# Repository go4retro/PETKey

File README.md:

# Commodore VIC/64 to PET/CBM Keyboard Adapter

## Hardware License

Copyright (C) 2021 Jim Brain and RETRO Innovations

These files are free designs; you can redistribute them and/or modify
them under the terms of the Creative Commons Attribution-ShareAlike 
4.0 International License.

You should have received a copy of the license along with this
work. If not, see <http://creativecommons.org/licenses/by-sa/4.0/>.

These files are distributed in the hope that they will be useful,
but WITHOUT ANY WARRANTY; without even the implied warranty of
MERCHANTABILITY or FITNESS FOR A PARTICULAR PURPOSE.  See the
license for more details.

## Software License

Copyright (C) 2021 Jim Brain and RETRO Innovations

These files are free designs; you can redistribute them and/or modify
them under the terms of the GNU General Public License, version 2 as 
published by the Free Software Foundation.

These files are distributed in the hope that they will be useful,
but WITHOUT ANY WARRANTY; without even the implied warranty of
MERCHANTABILITY or FITNESS FOR A PARTICULAR PURPOSE.  See the
GNU General Public License for more details.

You should have received a copy of the GNU General Public License along
with these files; if not, write to the Free Software Foundation, Inc.,
51 Franklin Street, Fifth Floor, Boston, MA 02110-1301 USA.

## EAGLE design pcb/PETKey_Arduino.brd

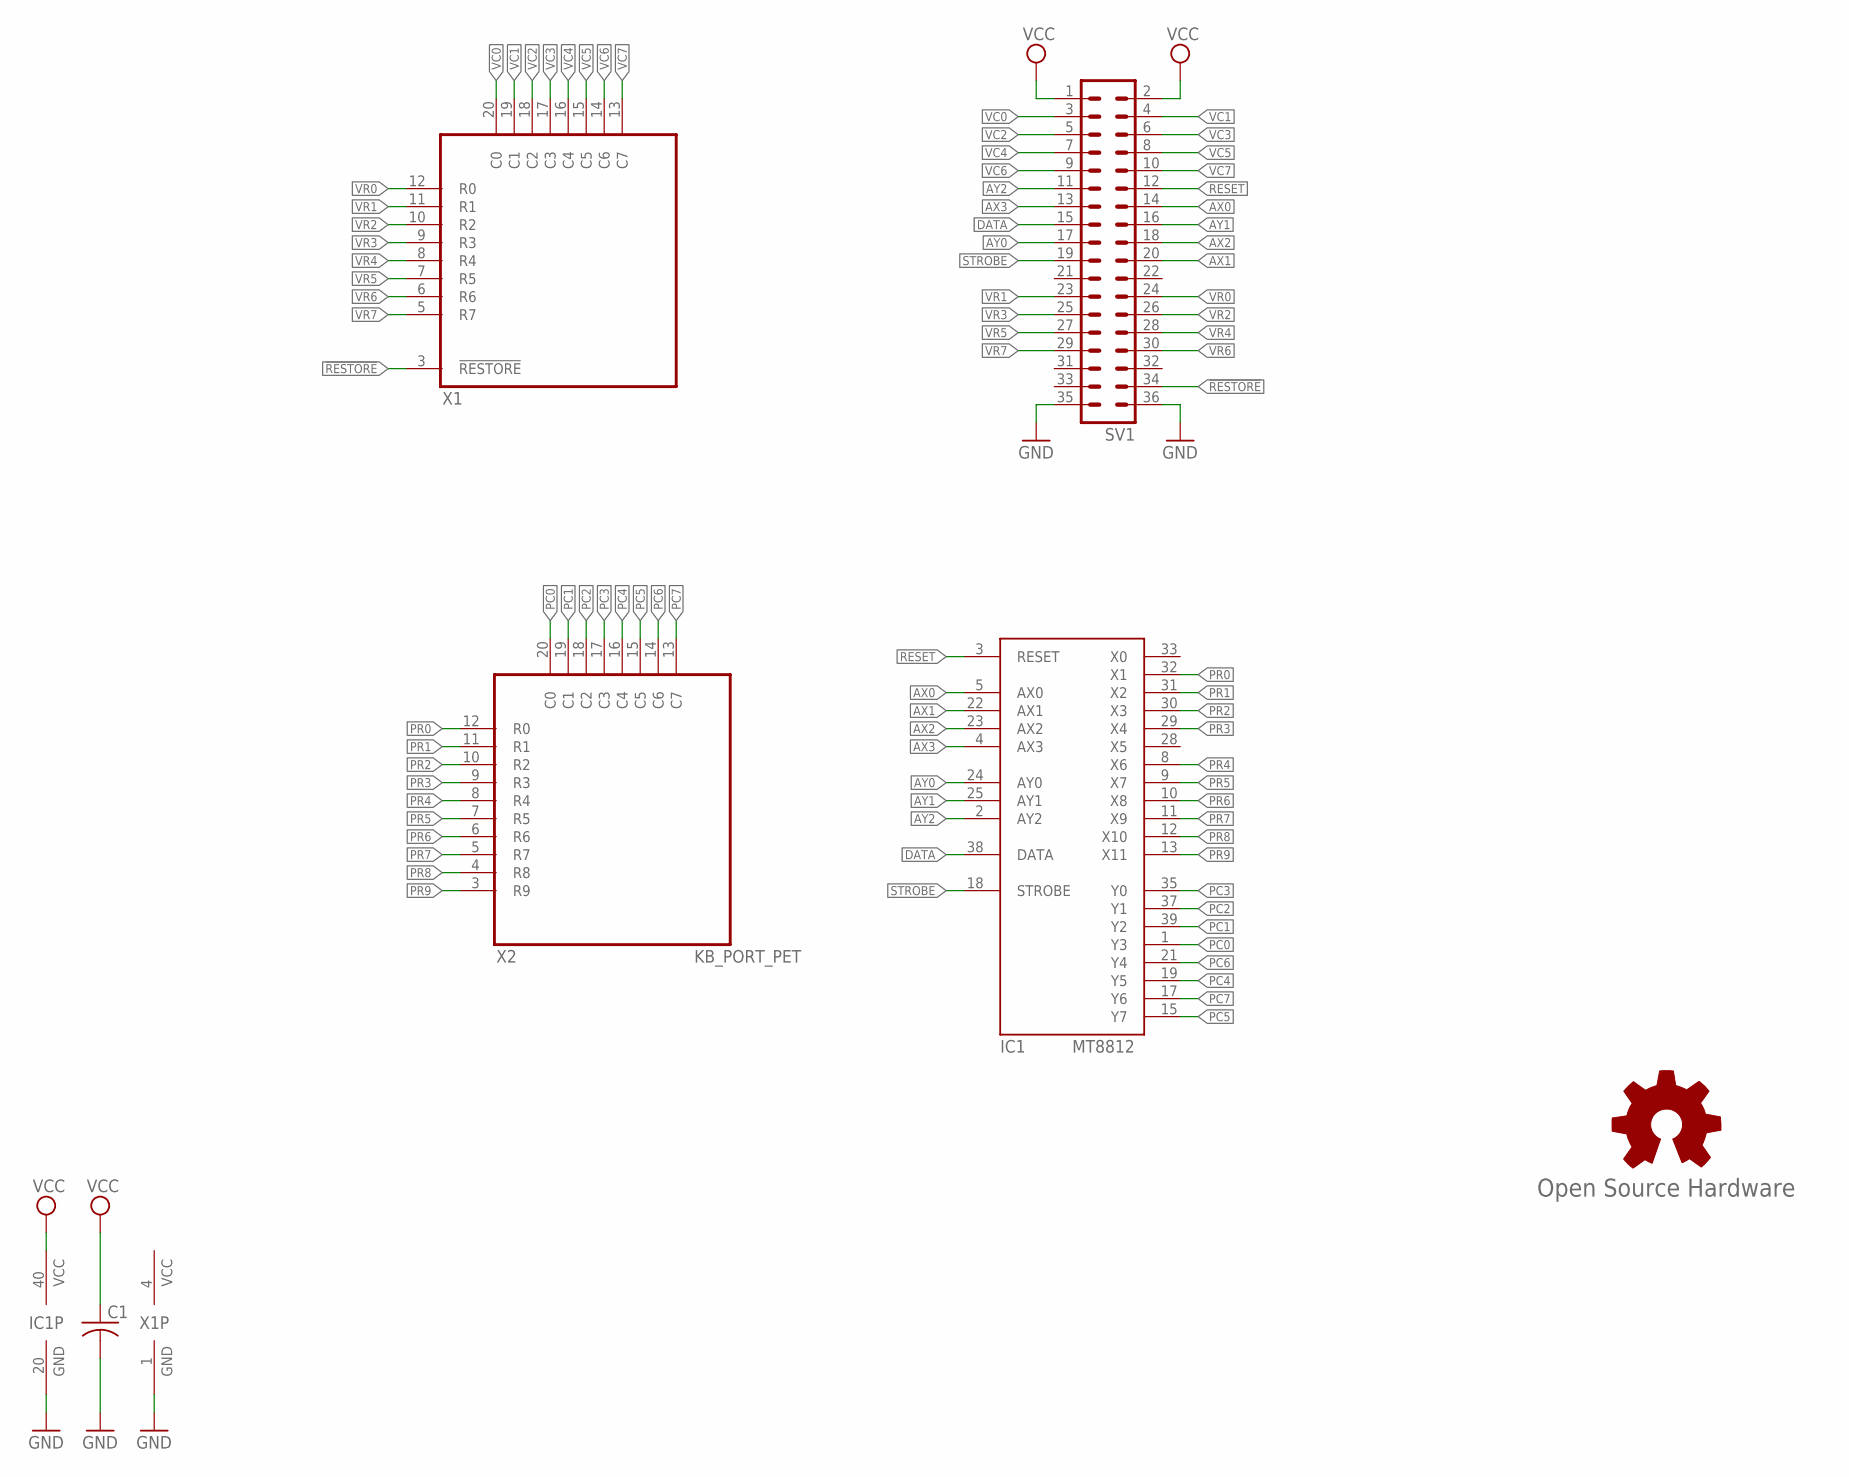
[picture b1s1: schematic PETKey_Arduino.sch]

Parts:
C1: C-US025-025X050; C025-025X050
GOLD_ORB_SM1: Open Source Hardware; OSHW_8MM
IC1: MT8812; DIP40
SV1: MA18-2
X1: KB_PORT_VIC/64; MA20-1_KEYED
X2: KB_PORT_PET; MA20-1_KEYED

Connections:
!RESTORE: SV1.34, X1.3 (!RESTORE)
AX0: IC1.5 (AX0), SV1.14
AX1: IC1.22 (AX1), SV1.20
AX2: IC1.23 (AX2), SV1.18
AX3: IC1.4 (AX3), SV1.13
AY0: IC1.24 (AY0), SV1.17
AY1: IC1.25 (AY1), SV1.16
AY2: IC1.2 (AY2), SV1.11
DATA: IC1.38 (DATA), SV1.15
GND: C1.2, IC1.20 (GND), SV1.35, SV1.36, X1.1 (GND), X2.1 (GND)
PC0: IC1.1 (Y3), X2.20 (C0)
PC1: IC1.39 (Y2), X2.19 (C1)
PC2: IC1.37 (Y1), X2.18 (C2)
PC3: IC1.35 (Y0), X2.17 (C3)
PC4: IC1.19 (Y5), X2.16 (C4)
PC5: IC1.15 (Y7), X2.15 (C5)
PC6: IC1.21 (Y4), X2.14 (C6)
PC7: IC1.17 (Y6), X2.13 (C7)
PR0: IC1.32 (X1), X2.12 (R0)
PR1: IC1.31 (X2), X2.11 (R1)
PR2: IC1.30 (X3), X2.10 (R2)
PR3: IC1.29 (X4), X2.9 (R3)
PR4: IC1.8 (X6), X2.8 (R4)
PR5: IC1.9 (X7), X2.7 (R5)
PR6: IC1.10 (X8), X2.6 (R6)
PR7: IC1.11 (X9), X2.5 (R7)
PR8: IC1.12 (X10), X2.4 (R8)
PR9: IC1.13 (X11), X2.3 (R9)
RESET: IC1.3 (RESET), SV1.12
STROBE: IC1.18 (STROBE), SV1.19
VC0: SV1.3, X1.20 (C0)
VC1: SV1.4, X1.19 (C1)
VC2: SV1.5, X1.18 (C2)
VC3: SV1.6, X1.17 (C3)
VC4: SV1.7, X1.16 (C4)
VC5: SV1.8, X1.15 (C5)
VC6: SV1.9, X1.14 (C6)
VC7: SV1.10, X1.13 (C7)
VCC: C1.1, IC1.40 (VCC), SV1.1, SV1.2, X1.4 (VCC)
VR0: SV1.24, X1.12 (R0)
VR1: SV1.23, X1.11 (R1)
VR2: SV1.26, X1.10 (R2)
VR3: SV1.25, X1.9 (R3)
VR4: SV1.28, X1.8 (R4)
VR5: SV1.27, X1.7 (R5)
VR6: SV1.30, X1.6 (R6)
VR7: SV1.29, X1.5 (R7)

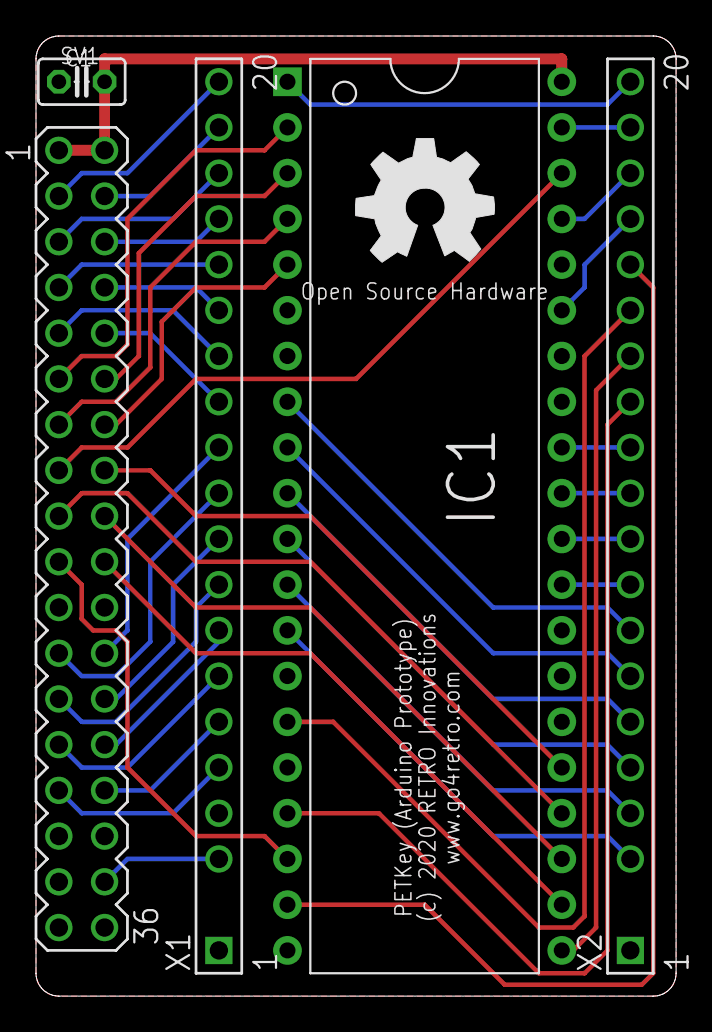
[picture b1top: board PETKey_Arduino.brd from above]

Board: 2 copper layers, 35.6 x 53.3 mm, 6 parts (0 on the bottom side), 47 nets.

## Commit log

2021-03-01 Initial import
2021-03-01 Small fix to code to compile in Arduino IDE
2021-03-01 Add in the rest of the PET keyboard mappings
2021-04-03 Comments cleanup and enable serial debugging
2021-04-03 Fix mapping for Commodore key
2021-04-03 More changes to mappings
2021-04-03 Initial PET Matrix mapping
2021-04-04 Debug code added
2021-04-04 Fix XPT mappings
2021-04-04 Debug sending '=' key
2021-04-04 Fix incorrect XPT mappings
2021-04-04 Macro cleanup and initial string code
2021-04-05 Refactored mappings into tables and reworked MOD_OVERRIDE behavior
2021-04-09 Mapping updates and fixes
2021-04-10 Fixed '-' and '=' mappings
2021-04-11 Potential fix for constant quotes bug
2021-04-11 strip modifiers off override key to un-depress
2021-04-18 Initial macro implementation
2021-04-18 Fix to handle shifted function key macros
2021-04-18 Map return to shift return when in config mode
2021-04-18 Remap regualr keys
2021-04-18 Fixed casing issue
2021-04-18 More case fixes
2021-04-18 Don't send shifted chars to PET in uppercase/gfx mode

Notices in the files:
pcb/PETKey_Arduino.brd:
(c) 2020 RETRO Innovations
